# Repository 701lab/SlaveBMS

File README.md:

# SlaveBMS
development of slave BMS

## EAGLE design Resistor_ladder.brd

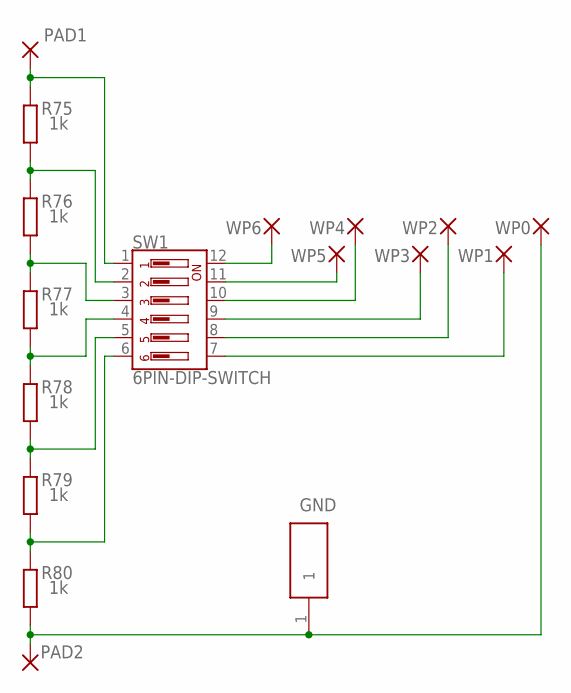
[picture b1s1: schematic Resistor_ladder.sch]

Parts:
GND: 5000
PAD1, PAD2: SMD_PAD
R75, R76, R77, R78, R79, R80: 1k; R0603
SW1: 6PIN-DIP-SWITCH; DIPSWITCH-06
WP0, WP1, WP2, WP3, WP4, WP5, WP6: 2,54/1,1

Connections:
unnamed: SW1.12, WP6.1
unnamed: SW1.11, WP5.1
unnamed: R77.2, R78.1, SW1.4
unnamed: SW1.10, WP4.1
unnamed: R76.2, R77.1, SW1.3
unnamed: R75.2, R76.1, SW1.2
unnamed: PAD1.1, R75.1, SW1.1
unnamed: GND.1, PAD2.1, R80.2, WP0.1
unnamed: R79.2, R80.1, SW1.6
unnamed: R78.2, R79.1, SW1.5
unnamed: SW1.9, WP3.1
unnamed: SW1.8, WP2.1
unnamed: SW1.7, WP1.1

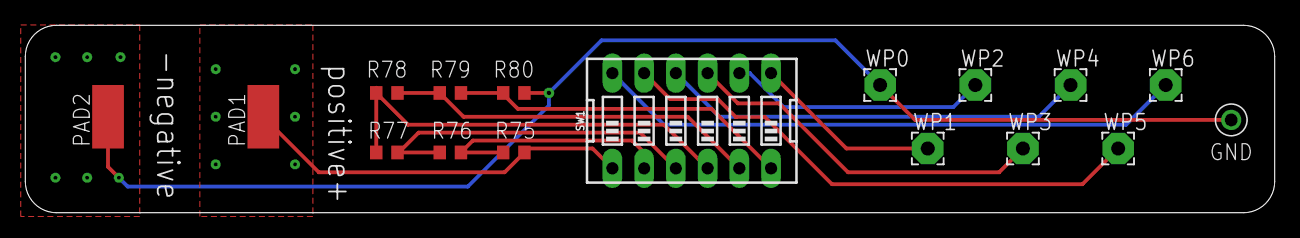
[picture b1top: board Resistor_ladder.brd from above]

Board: 4 copper layers, 100.0 x 15.0 mm, 17 parts (0 on the bottom side), 13 nets.

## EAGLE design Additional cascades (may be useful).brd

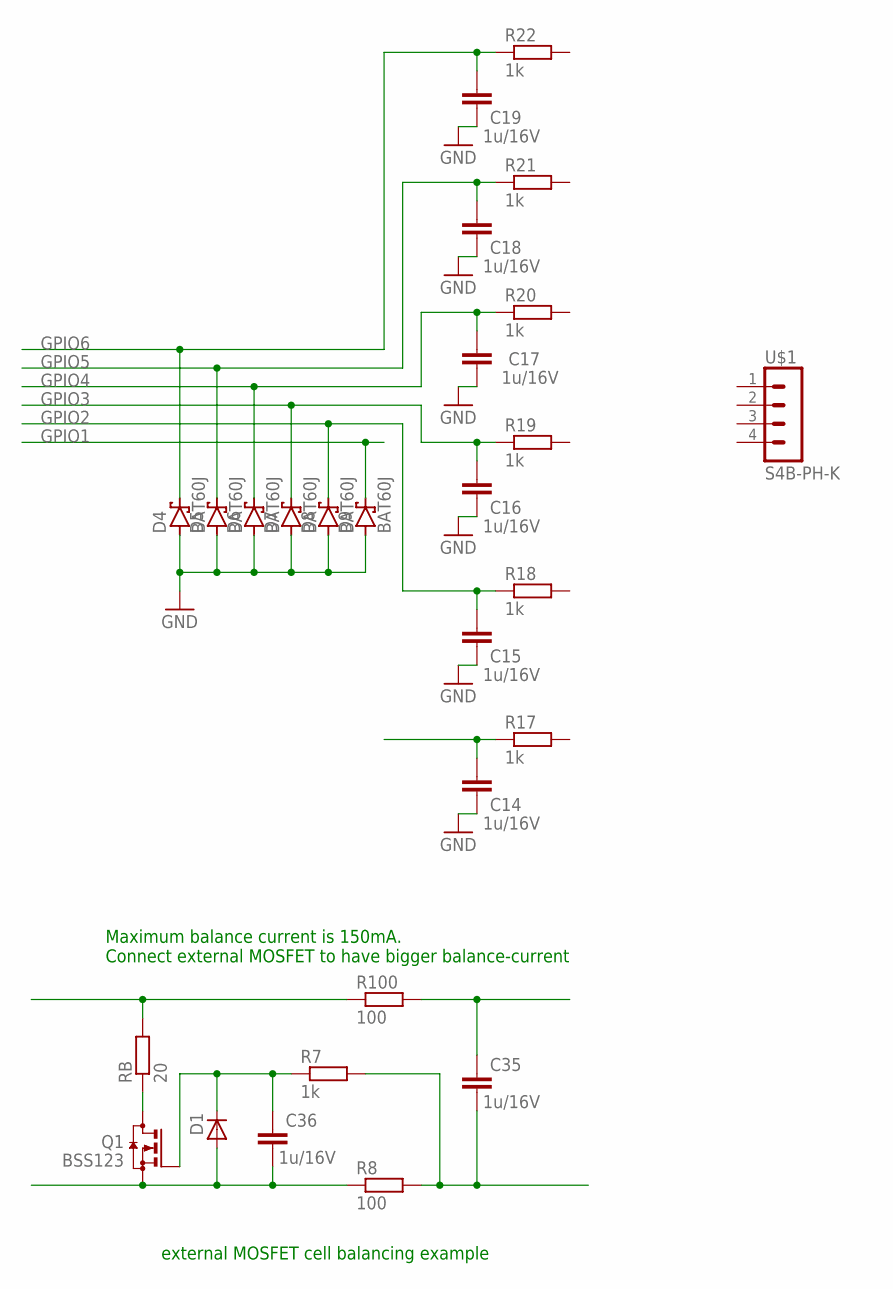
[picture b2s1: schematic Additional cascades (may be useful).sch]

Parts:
C14, C15, C16, C17, C18, C19, C35, C36: 1u/16V; C0603
D1: DIODE_E-; DIODE_SMB
D4, D5, D6, D7, D8, D9: BAT60J; SOD323_ST
Q1: BSS123; SOT23
R7, R17, R18, R19, R20, R21, R22: 1k; R0603
R8, R100: 100; R0603
RB: 20; R0603
U$1: S4B-PH-K

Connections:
GND: C14.1, C15.1, C16.1, C17.1, C18.1, C19.1, D4.A, D5.A, D6.A, D7.A, D8.A, D9.A
GPIO1: C14.2, D9.C, R17.1
GPIO2: C15.2, D8.C, R18.1
GPIO3: C16.2, D7.C, R19.1
GPIO4: C17.2, D6.C, R20.1
GPIO5: C18.2, D5.C, R21.1
GPIO6: C19.2, D4.C, R22.1
unnamed: Q1.3 (D), RB.1
unnamed: R100.1, RB.2
unnamed: C35.2, R100.2
unnamed: C35.1, R7.2, R8.2
unnamed: C36.1, D1.A (C), Q1.2 (S), R8.1
unnamed: C36.2, D1.C (A), Q1.1 (G), R7.1

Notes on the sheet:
external MOSFET cell balancing example
Maximum balance current is 150mA. Connect external MOSFET to have bigger balance-current

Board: 2 copper layers, 28 parts (0 on the bottom side), 13 nets, no tracks yet.

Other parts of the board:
U$2: BMS_HIGH_COM

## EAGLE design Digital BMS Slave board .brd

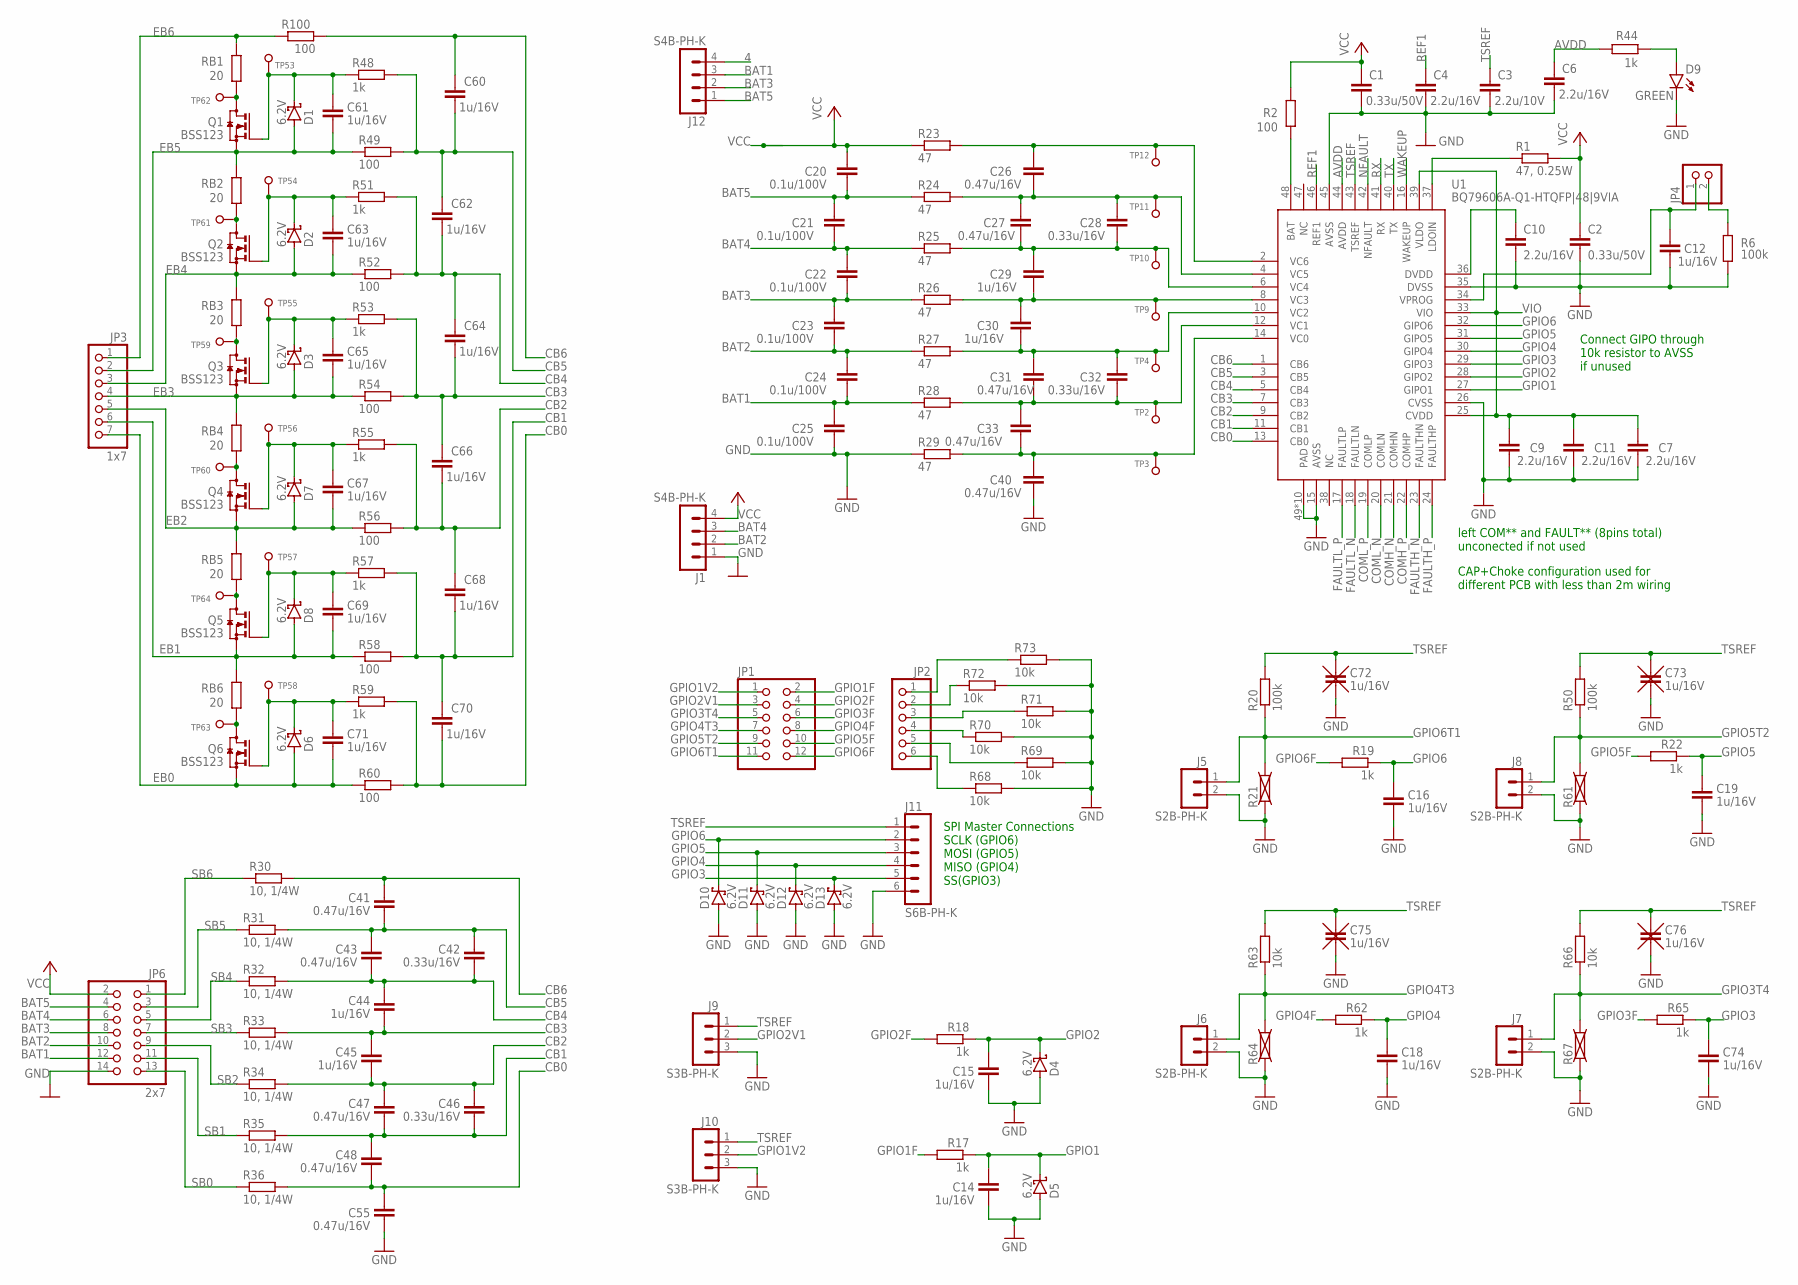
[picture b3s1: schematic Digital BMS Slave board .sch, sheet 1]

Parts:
C1, C2: 0.33u/50V; C1206K
C3: 2.2u/10V; C0603
C4, C6, C7, C9, C10, C11: 2.2u/16V; C0603
C12, C14, C15, C16, C18, C19, C60, C61, C62, C63, C64, C65, C66, C67, C68, C69, C70, C71, C74: 1u/16V; C0603
C20, C21, C22, C23, C24, C25: 0.1u/100V; C1206K
C26, C27, C31, C33, C40, C41, C43, C47, C48, C55: 0.47u/16V; C0603
C28, C32, C42, C46: 0.33u/16V; C0603
C29, C30, C44, C45: 1u/16V; C0805K
C72, C73, C75, C76: 1u/16V; C0603K-X
D1, D2, D3, D4, D5, D6, D7, D8, D10, D11, D12, D13: 6.2V; SOD323_ST
D9: GREEN; LED-0805
J1, J12: S4B-PH-K
J5, J6, J7, J8: S2B-PH-K
J9, J10: S3B-PH-K
J11: S6B-PH-K
JP1: PINHD-2X6; 2X06
JP2: PINHD-1X6-OCT; 1X06
JP3: 1x7; 1X07
JP4: PINHD-1X2; 1X02
JP6: 2x7; 2X07
Q1, Q2, Q3, Q4, Q5, Q6: BSS123; SOT23
R1: 47, 0.25W; R1206
R2, R49, R52, R54, R56, R58, R60, R100: 100; R0603
R6, R20, R50: 100k; R0603
R17, R18, R19, R22, R44, R48, R51, R53, R55, R57, R59, R62, R65: 1k; R0603
R21, R61, R64, R67: R-EU-X0603; R0603-X
R23, R24, R25, R26, R27, R28, R29: 47; R0603
R30, R31, R32, R33, R34, R35, R36: 10, 1/4W; R1210
R63, R66, R68, R69, R70, R71, R72, R73: 10k; R0603
RB1, RB2, RB3, RB4, RB5, RB6: 20; R2512
TP2, TP3, TP4, TP9, TP10, TP11, TP12: TEST_PAD-[1MM]; TP1MM_MASK
TP53, TP54, TP55, TP56, TP57, TP58, TP59, TP60, TP61, TP62, TP63, TP64: TEST_PAD-[1.27MM]; TP1.27MM
U1: BQ79606A-Q1-HTQFP|48|9VIA; HTQFP48-9X9MM-VIA

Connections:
4: J12.4
AVDD: C6.1, R44.2, U1.44 (AVDD)
BAT: R2.1, U1.48 (BAT)
BAT1: C24.1, C25.2, J12.3, JP6.12, R28.1
BAT2: C23.1, C24.2, J1.2, JP6.10, R27.1
BAT3: C22.1, C23.2, J12.2, JP6.8, R26.1
BAT4: C21.1, C22.2, J1.3, JP6.6, R25.1
BAT5: C20.1, C21.2, J12.1, JP6.4, R24.1
CB0: C48.1, C55.2, C70.1, R36.2, R59.2, R60.2, U1.13 (CB0)
CB1: C46.1, C47.1, C48.2, C68.1, C70.2, R35.2, R57.2, R58.2, U1.11 (CB1)
CB2: C45.1, C46.2, C47.2, C66.1, C68.2, R34.2, R55.2, R56.2, U1.9 (CB2)
CB3: C44.1, C45.2, C64.1, C66.2, R33.2, R53.2, R54.2, U1.7 (CB3)
CB4: C42.1, C43.1, C44.2, C62.1, C64.2, R32.2, R51.2, R52.2, U1.5 (CB4)
CB5: C41.1, C42.2, C43.2, C60.1, C62.2, R31.2, R48.2, R49.2, U1.3 (CB5)
CB6: C41.2, C60.2, R30.2, R100.2, U1.1 (CB6)
COMH_N: U1.21 (COMHN); also elsewhere on the board
COMH_P: U1.22 (COMHP); also elsewhere on the board
COML_N: U1.20 (COMLN); also elsewhere on the board
COML_P: U1.19 (COMLP); also elsewhere on the board
DVDD: C10.1, U1.36 (DVDD)
EB0: C71.1, D6.A, JP3.7, Q6.2 (S), R60.1
EB1: C69.1, D8.A, JP3.6, Q5.2 (S), R58.1, RB6.2
EB2: C67.1, D7.A, JP3.5, Q4.2 (S), R56.1, RB5.2
EB3: C65.1, D3.A, JP3.4, Q3.2 (S), R54.1, RB4.2
EB4: C63.1, D2.A, JP3.3, Q2.2 (S), R52.1, RB3.2
EB5: C61.1, D1.A, JP3.2, Q1.2 (S), R49.1, RB2.2
EB6: JP3.1, R100.1, RB1.2
FAULTH_N: U1.23 (FAULTHN); also elsewhere on the board
FAULTH_P: U1.24 (FAULTHP); also elsewhere on the board
FAULTL_N: U1.18 (FAULTLN); also elsewhere on the board
FAULTL_P: U1.17 (FAULTLP); also elsewhere on the board
GND: C1.1, C2.2, C3.2, C4.2, C6.2, C7.2, C9.2, C10.2, C11.2, C12.2, C14.1, C15.1, C16.1, C18.1, C19.1, C25.1, C40.1, C55.1, C72.2, C73.2, C74.1, C75.2, C76.2, D4.A, D5.A, D9.- (C), D10.A, D11.A, D12.A, D13.A, J1.1, J5.2, J6.2, J7.2, J8.2, J9.3, J10.3, J11.6, JP6.14, R6.1, R21.1, R29.1, R61.1, R64.1, R67.1, R68.2, R69.2, R70.2, R71.2, R72.2, R73.2, U1.15 (AVSS), U1.26 (CVSS), U1.35 (DVSS), U1.45 (AVSS), U1.49 (PAD), U1.491 (PAD), U1.492 (PAD), U1.493 (PAD), U1.494 (PAD), U1.495 (PAD), U1.496 (PAD), U1.497 (PAD), U1.498 (PAD), U1.499 (PAD); also elsewhere on the board
GPIO1: C14.2, D5.C, R17.1, U1.27 (GIPO1)
GPIO1F: JP1.2, R17.2
GPIO1V2: J10.2, JP1.1
GPIO2: C15.2, D4.C, R18.1, U1.28 (GIPO2)
GPIO2F: JP1.4, R18.2
GPIO2V1: J9.2, JP1.3
GPIO3: C74.2, D13.C, J11.5, R65.1, U1.29 (GIPO3)
GPIO3F: JP1.6, R65.2
GPIO3T4: J7.1, JP1.5, R66.1, R67.2
GPIO4: C18.2, D12.C, J11.4, R62.1, U1.30 (GIPO4)
GPIO4F: JP1.8, R62.2
GPIO4T3: J6.1, JP1.7, R63.1, R64.2
GPIO5: C19.2, D11.C, J11.3, R22.1, U1.31 (GIPO5)
GPIO5F: JP1.10, R22.2
GPIO5T2: J8.1, JP1.9, R50.1, R61.2
GPIO6: C16.2, D10.C, J11.2, R19.1, U1.32 (GIPO6)
GPIO6F: JP1.12, R19.2
GPIO6T1: J5.1, JP1.11, R20.1, R21.2
LDOIN: R1.1, U1.37 (LDOIN)
unnamed: JP4.2, R6.2
unnamed: Q1.3 (D), RB1.1, TP62.1
unnamed: JP2.1, R73.1
unnamed: JP2.2, R72.1
unnamed: JP2.3, R71.1
unnamed: JP2.4, R70.1
unnamed: Q3.3 (D), RB3.1, TP59.1
unnamed: JP2.5, R69.1
unnamed: JP2.6, R68.1
unnamed: D9.+ (A), R44.1
unnamed: C61.2, D1.C, Q1.1 (G), R48.1, TP53.1
unnamed: Q2.3 (D), RB2.1, TP61.1
unnamed: Q5.3 (D), RB5.1, TP64.1
unnamed: C63.2, D2.C, Q2.1 (G), R51.1, TP54.1
unnamed: C65.2, D3.C, Q3.1 (G), R53.1, TP55.1
unnamed: Q4.3 (D), RB4.1, TP60.1
unnamed: C67.2, D7.C, Q4.1 (G), R55.1, TP56.1
unnamed: C69.2, D8.C, Q5.1 (G), R57.1, TP57.1
unnamed: Q6.3 (D), RB6.1, TP63.1
unnamed: C71.2, D6.C, Q6.1 (G), R59.1, TP58.1
NFAULT: U1.42 (NFAULT); also elsewhere on the board
REF1: C4.1, U1.46 (REF1)
RX: U1.41 (RX); also elsewhere on the board
SB0: JP6.13, R36.1
SB1: JP6.11, R35.1
SB2: JP6.9, R34.1
SB3: JP6.7, R33.1
SB4: JP6.5, R32.1
SB5: JP6.3, R31.1
SB6: JP6.1, R30.1
TSREF: C3.1, C72.1, C73.1, C75.1, C76.1, J9.1, J10.1, J11.1, R20.2, R50.2, R63.2, R66.2, U1.43 (TSREF)
TX: U1.40 (TX); also elsewhere on the board
VC0: C33.1, C40.2, R29.2, TP3.1, U1.14 (VC0)
VC1: C31.1, C32.1, C33.2, R28.2, TP2.1, U1.12 (VC1)
VC2: C30.1, C31.2, C32.2, R27.2, TP4.1, U1.10 (VC2)
VC3: C29.1, C30.2, R26.2, TP9.1, U1.8 (VC3)
VC4: C27.1, C28.1, C29.2, R25.2, TP10.1, U1.6 (VC4)
VC5: C26.1, C27.2, C28.2, R24.2, TP11.1, U1.4 (VC5)
VC6: C26.2, R23.2, TP12.1, U1.2 (VC6)
VCC: C1.2, C2.1, C20.2, J1.4, JP6.2, R1.2, R2.2, R23.1
VIO: C7.1, C9.1, C11.1, U1.25 (CVDD), U1.33 (VIO), U1.39 (VLDO); also elsewhere on the board
VPROG: C12.1, JP4.1, U1.34 (VPROG)
WAKEUP: U1.16 (WAKEUP); also elsewhere on the board

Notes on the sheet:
Connect GIPO through 10k resistor to AVSS if unused
left COM** and FAULT** (8pins total) unconected if not used
CAP+Choke configuration used for different PCB with less than 2m wiring
SPI Master Connections SCLK (GPIO6) MOSI (GPIO5) MISO (GPIO4) SS(GPIO3)

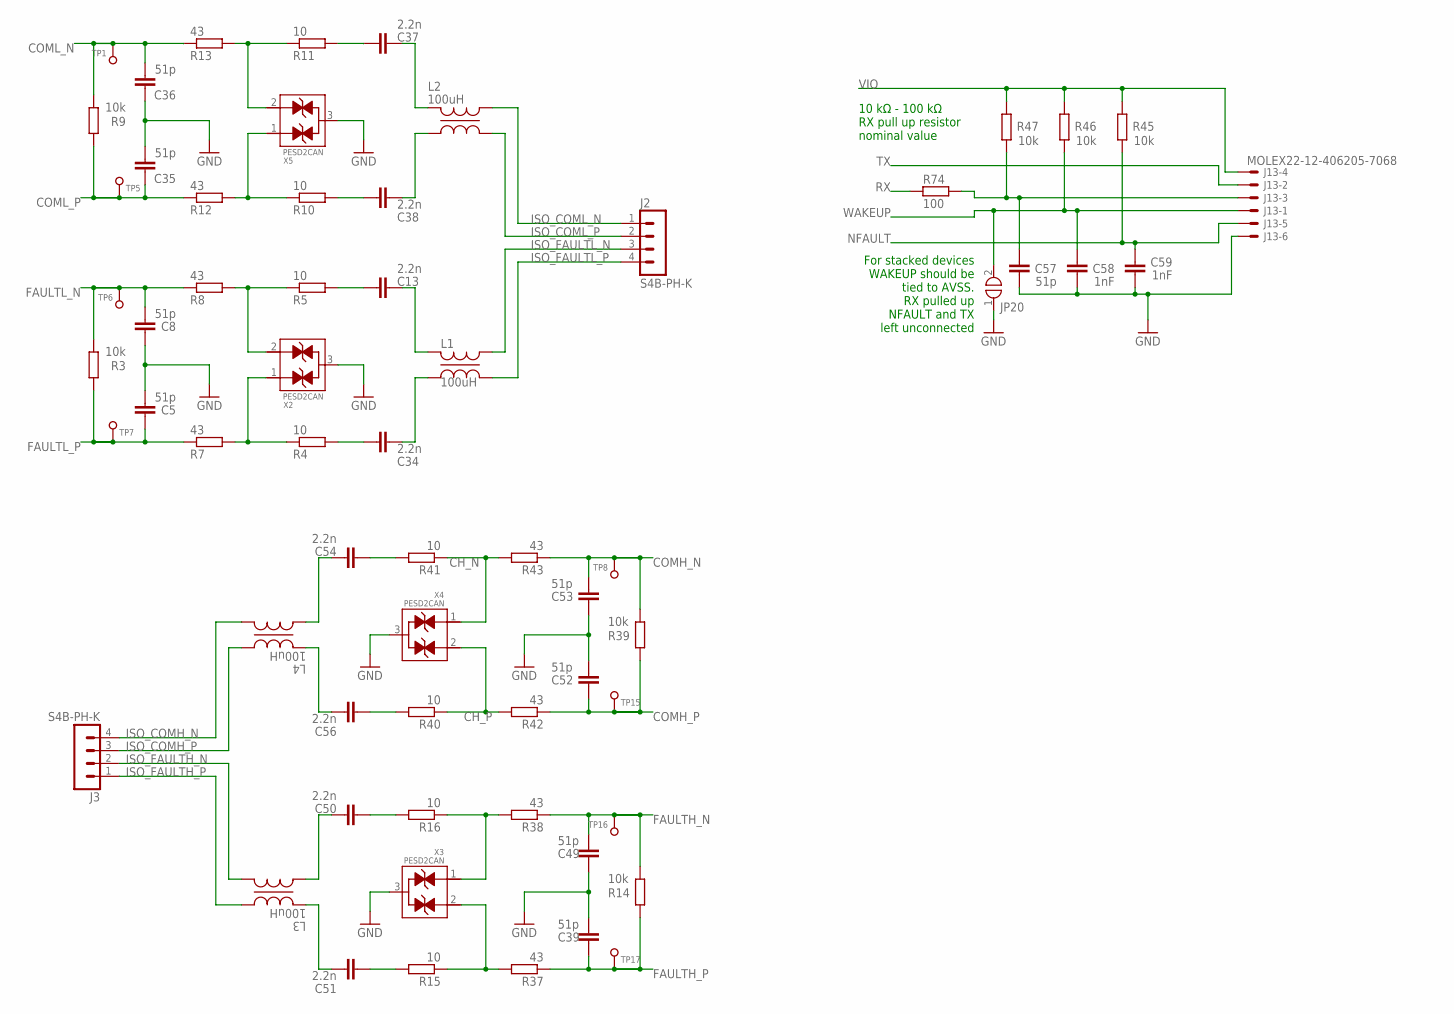
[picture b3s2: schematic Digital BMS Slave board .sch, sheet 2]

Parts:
C5, C8, C35, C36, C39, C49, C52, C53, C57: 51p; C0603
C13, C34, C37, C38, C50, C51, C54, C56: 2.2n; C1206K
C58, C59: 1nF; C0603
J2, J3: S4B-PH-K
J13: MOLEX22-12-406205-7068; 7395-06
JP20: SOLDER_BRIDGE
L1, L2, L3, L4: 100uH; ACT45B
R3, R9, R14, R39, R45, R46, R47: 10k; R0603
R4, R5, R10, R11, R15, R16, R40, R41: 10; R0603
R7, R8, R12, R13, R37, R38, R42, R43: 43; R0603
R74: 100; R0603
TP1, TP5, TP6, TP7, TP8, TP15, TP16, TP17: TEST_PAD-[1MM]; TP1MM_MASK
X2, X3, X4, X5: PESD2CAN; SOT23

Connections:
CH1_N: C54.2, R41.2
CH1_P: C56.2, R40.2
CH2_N: C54.1, L4.2
CH2_P: C56.1, L4.1
CH_N: R41.1, R43.2, X4.1
CH_P: R40.1, R42.2, X4.2
CL1_N: C37.2, R11.2
CL1_P: C38.2, R10.2
CL2_N: C37.1, L2.1
CL2_P: C38.1, L2.2
CL_N: R11.1, R13.2, X5.2
CL_P: R10.1, R12.2, X5.1
COMH_N: C53.2, R39.1, R43.1, TP8.1; also elsewhere on the board
COMH_P: C52.2, R39.2, R42.1, TP15.1; also elsewhere on the board
COML_N: C36.2, R9.1, R13.1, TP1.1; also elsewhere on the board
COML_P: C35.2, R9.2, R12.1, TP5.1; also elsewhere on the board
FAULTH_N: C49.2, R14.1, R38.1, TP16.1; also elsewhere on the board
FAULTH_P: C39.2, R14.2, R37.1, TP17.1; also elsewhere on the board
FAULTL_N: C8.2, R3.1, R8.1, TP6.1; also elsewhere on the board
FAULTL_P: C5.2, R3.2, R7.1, TP7.1; also elsewhere on the board
FH1_N: C50.2, R16.2
FH1_P: C51.2, R15.2
FH2_N: C50.1, L3.2
FH2_P: C51.1, L3.1
FH_N: R16.1, R38.2, X3.1
FH_P: R15.1, R37.2, X3.2
FL1_N: C13.2, R5.2
FL1_P: C34.2, R4.2
FL2_N: C13.1, L1.1
FL2_P: C34.1, L1.2
FL_N: R5.1, R8.2, X2.2
FL_P: R4.1, R7.2, X2.1
GND: C5.1, C8.1, C35.1, C36.1, C39.1, C49.1, C52.1, C53.1, C57.1, C58.1, C59.1, J13.6, JP20.1, X2.3, X3.3, X4.3, X5.3; also elsewhere on the board
ISO_COMH_N: J3.4, L4.3
ISO_COMH_P: J3.3, L4.4
ISO_COML_N: J2.1, L2.4
ISO_COML_P: J2.2, L2.3
ISO_FAULTH_N: J3.2, L3.3
ISO_FAULTH_P: J3.1, L3.4
ISO_FAULTL_N: J2.3, L1.4
ISO_FAULTL_P: J2.4, L1.3
NFAULT: C59.2, J13.5, R45.1; also elsewhere on the board
RX: R74.2; also elsewhere on the board
RX1: C57.2, J13.3, R47.1, R74.1
TX: J13.2; also elsewhere on the board
VIO: J13.4, R45.2, R46.2, R47.2; also elsewhere on the board
WAKEUP: C58.2, J13.1, JP20.2, R46.1; also elsewhere on the board

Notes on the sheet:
For stacked devices WAKEUP should be tied to AVSS. RX pulled up NFAULT and TX left unconnected
10 kΩ - 100 kΩ RX pull up resistor nominal value

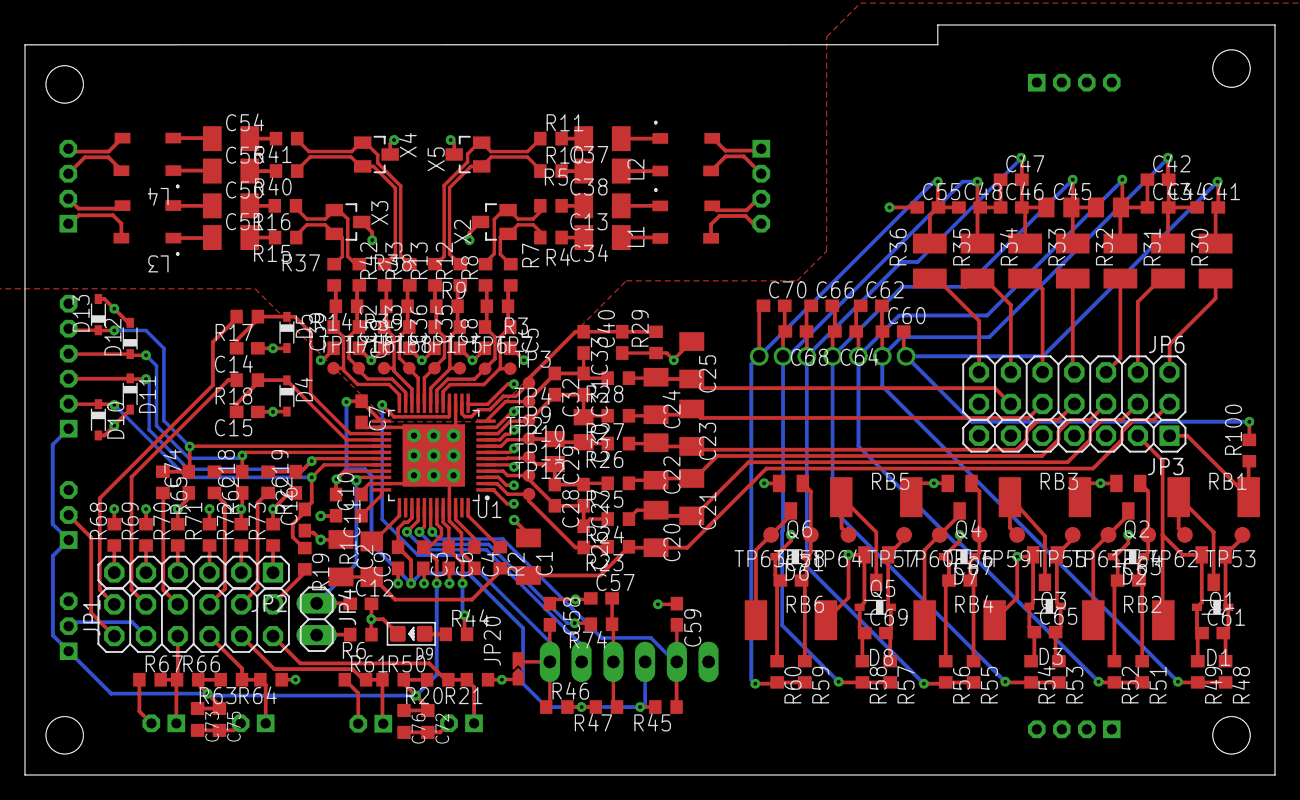
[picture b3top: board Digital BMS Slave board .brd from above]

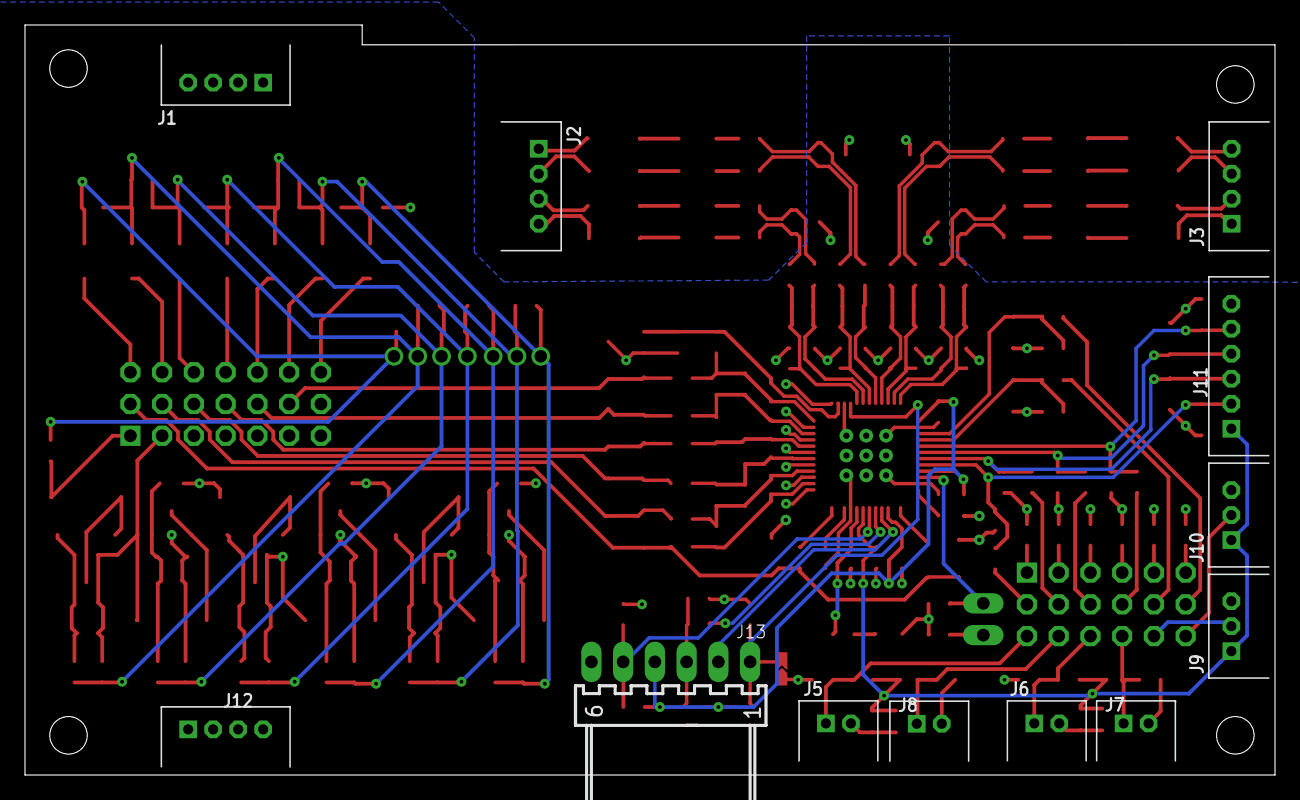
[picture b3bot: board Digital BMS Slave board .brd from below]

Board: 4 copper layers, 100.0 x 60.0 mm, 229 parts (12 on the bottom side), 126 nets.

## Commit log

2019-09-09 added eagleCAD ignore
2019-09-09 First Uploading Files
2019-09-09 test
2019-09-09 some edits
2019-09-21 Board size to chek
    The schematic file is close to release ver.
2019-09-21 3d models fixed
2019-10-02 Schematic in accordance with BOM
2019-10-02 Footprint fixed
2019-11-04 components placed on board
2019-11-06 Go home
2019-11-07 COM and IC CAP routed
2019-11-08 GPIO routed
2019-11-09 Full routing 1.0ver. to review
    DRC rules checked
2019-11-22 Ready to generte GERBER
    Silkscreen+improvements
2019-11-28 Some components names changed
    BOM generated
2019-12-22 layer numbers added
2019-12-22 frame with tab routing added
2019-12-24 communication fail correction
2019-12-24 Cam without frame generated
2019-12-24 silkscreen top fail removed
2019-12-26 Resistor ladder added as a panel
2019-12-26 changes for testing puposes
2019-12-27 VPROG pads added
2020-01-02 Test rings for voltage sensing added
2020-01-08 Connectors to resistor ladder added
2020-01-10 Isolation IC added. Power trace fixed
2020-01-20 assembly drawing
2020-01-22 pull up at isolation side
2020-02-07 CAM outputs
2020-02-20 Gerbers for first order
2020-02-23 drill changed to 3.2
2020-02-25 ready to manufacturing
2020-03-28 ESCD
2020-05-03 Some changes
    I don't know

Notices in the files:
parts and their libraries:
con-jst-ph: Copyright (C) 2016, Bob Starr
